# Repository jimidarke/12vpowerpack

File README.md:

# 12 V power pack

A small in-vehicle UPS on one PCB: a 12 V sealed AGM battery floated on the car's charging voltage, a pass-through 12 V output and a 5 V USB-A output that keep running from the battery for a set time after the ignition goes off.

## Status

Design phase. The requirements and architecture were cut back to this vehicle-only design (v3) on 2026-11-13, and the schematic was captured in Flux and checked against the net table that day. On 2026-11-14 the parts were trimmed for a DIY batch of 5 (v3.1), and the schematic was updated and re-checked (77 parts). Later that day capture moved to KiCad 10: the schematic is generated from the net table, and the 100 × 70 mm board is placed, has its first routing pass (power pours and autorouted signals, DRC clean) and carries its silkscreen labels. The routing fixes from the first review, thermal vias and fiducials are in; the checks against parts in hand are still to do (`kicad/README.md`). Nothing has been built or tested. Values marked **[TBC]** in `architecture.md` are still to be confirmed. The earlier two-chemistry design (v2) is in git at tag `v0.2.1`.

## Specification

- **Input:** ignition-switched car 12 V, 13.8–14.4 V nominal with the engine running and 11–14.8 V working. The board starts at about 12.1 V (11.5–12.7 V across part tolerances); once running, the battery carries it through dips and cranking. It is reverse-polarity protected, clamped above 18 V, and the input fuse blows on a sustained 20–22 V. About 5 A continuous and 7 A peak. The battery never feeds back into the car. Not for mains adapters.
- **Battery:** 12 V sealed AGM, 2–12 Ah, charged from the car feed through a current-limiting resistor. There is no charger IC.
- **12 V output:** unregulated: the car feed or the battery less 0.1–0.5 V, so about 10.8–14.8 V (9.9 V worst case at a 5 A peak near the cutoff). 3 A continuous with 5 A peaks, 5.5 mm barrel jack. A car-side fault passes through, up to about 22 V (29 V during a clamped surge).
- **5 V output:** 5.02 V (4.86–5.17 V worst case), 2 A USB-A for loads such as a Pi, router or camera (D+ tied to D−, no charging-port IC).
- **Power control:** outputs stay on for an adjustable time after ignition-off (a firmware setting, default 30 min; 0 = no timeout), then everything switches off until the ignition returns. A hardware low-voltage cutoff near 11.0 V (10.5–11.45 V across part tolerances) protects the battery.

The full voltage and power budget is in [`architecture.md`](architecture.md#voltage-and-power-budget-calc).
- **Monitoring:** socketed Seeed XIAO ESP32-C6 running ESPHome, reporting car voltage, battery voltage, battery temperature, and power in and out from two INA226 current monitors. Red and green status LEDs. No display.
- **Safety:** fuses, the charge limit, reverse-polarity blocking and the low-voltage cutoff are hardware. The board stays safe with the ESP32 removed.
- **Environment:** parts rated −40 to 85 °C.

Full details are in [`requirements.md`](requirements.md).

## Block diagram

```
Car 12 V in ─ fuse ─ TVS ─ ideal diode ─ SYS ─┬─ switch ─ fuse ─ 12 V barrel jack
                                              ├─ 5 V buck ─ USB-A, ESP32
                                              ├─ fuse ─ charge resistor ─┐
                                              └─ ideal diode ────────────┴─ fuse ─ AGM battery
```

## Main parts

| Function | Part |
|---|---|
| Input and battery ideal diodes | TI LM74700-Q1 ×2 with CSD18543Q3A FETs |
| Surge clamp | SMCJ18CA |
| 12 V output switch | Diodes DMP4015SK3 |
| 5 V rail and low-voltage cutoff | TI LMR33630 |
| Current monitors | TI INA226 ×2 |
| Controller | Seeed XIAO ESP32-C6 |
| Battery temperature | DS18B20 probe |

## Repository layout

| Path | Contents |
|---|---|
| [`requirements.md`](requirements.md) | What the board must do |
| [`architecture.md`](architecture.md) | Block diagram, net names, values, power control, voltage and power budget, ESP32 pin map, connectors |
| [`netlist.md`](netlist.md) | Pin-by-pin net table the KiCad schematic is generated from and checked against |
| [`kicad/`](kicad) | KiCad 10 project: generated schematic, board, project library, generator and check scripts ([README](kicad/README.md)) |
| [`plan.md`](plan.md) | Status, part-choice reasoning, cost estimate, how the capture was done, bench test plan |
| [`blocks/`](blocks) | Placement plan (`04-placement*`), layout brief, and the Flux messages and edit lists (history); `retired/` holds the v2 briefs |
| [`datasheets/`](datasheets) | Text extracts of the datasheets the values were taken from |
| [`flux-log.md`](flux-log.md) | Log of the Flux agent runs and credits (Flux archived 2026-11-14) |

The schematic and board are in KiCad 10 (`kicad/`). The earlier Flux capture ([project](https://www.flux.ai/jimidarke/12v-power-manager~zn)) is archived.

## Cost target

≤ C$110 per board at a batch of 5, excluding battery and enclosure. The current price checkpoint is in [`plan.md`](plan.md): the fab fits the SMT parts and the owner hand-solders the through-hole parts and a few easy SMT ones.

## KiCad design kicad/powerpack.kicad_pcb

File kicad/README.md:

# KiCad project

KiCad 10 project for the board: `powerpack.kicad_pro`. Open it in KiCad 10.0.x; the Linux box that generates and checks the files runs 10.0.8, so keep both machines on the same major version.

## Files

| File | Who edits it | What it is |
|---|---|---|
| `powerpack.kicad_sch` | generated: `gen/gen_sch.py` | Schematic, one A2 sheet, one dashed box per module. Every pin carries a net label; there are no wires between parts. **Edit `../netlist.md`, not this file.** |
| `powerpack.kicad_pcb` | the owner, in KiCad | Board. Written once by `gen/gen_pcb.py`, then re-placed on 2026-11-14 by `gen/place_pcb.py` at the owner's request (100 × 70 mm, parts spread out, every label in a clear spot). First routing pass and silkscreen pass (`gen/silk_pcb.py`) on 2026-11-14. Edited by hand from here on, except the silkscreen labels, which come from `silk_pcb.py`; `place_pcb.py` refuses to run once the board has tracks. |
| `powerpack.kicad_pro` | KiCad, plus `gen_pcb.py` once | Project settings, net classes (`Power`: 1.5 mm tracks and 0.8/0.4 mm vias on the power path and GND; `Default`: 0.25 mm; both 0.13 mm clearance, the pours 0.3 mm) and JLCPCB minimums. |
| `sym-lib-table`, `fp-lib-table` | fixed | Add the project library `pwrpack` with `${KIPRJMOD}` paths, so it works on Windows and Linux. |
| `lib/pwrpack.*` | generated: `gen/build_lib.py`, and `gen/build_models.py` for three 3D models | Project symbols (XIAO ESP32-C6, Keystone 3557-2 holder, DMP4015SK3) and footprints (XIAO on two 1×7 sockets, AC10 52 mm, SRP6540, 3557-2, Würth USB-A), with 3D models. |
| `lib/lcsc.*` | `easyeda2kicad` | Raw LCSC downloads that `build_lib.py` converts. The 3D folder is not in git. |
| `out/` | generated, not in git | `expected.json`, KiCad netlist, ERC and DRC reports. |

Every other part uses the stock KiCad 10 libraries.

## Working together over git

- One editor per file. The Linux side regenerates the schematic; the owner owns the board. Don't edit `powerpack.kicad_sch` by hand: the next regeneration overwrites it.
- Close KiCad before `git pull`, reopen after.
- A schematic change: edit `../netlist.md`, run the two scripts below, push. On the laptop: pull, open the board, **Tools → Update PCB from Schematic**. The footprints carry the schematic symbol IDs, so placement and routing are kept.
- `*.kicad_prl` (per-user view state), backups and lock files are in `.gitignore`. `.gitattributes` keeps the KiCad files on LF line endings.

## Commands (Linux box)

```
python3 kicad/gen/gen_sch.py      # netlist.md -> powerpack.kicad_sch
python3 kicad/gen/check_sch.py    # upgrade to the native format, ERC, compare KiCad's netlist with netlist.md
kicad-cli pcb drc --schematic-parity -o kicad/out/drc.rpt kicad/powerpack.kicad_pcb
python3 kicad/gen/build_lib.py    # only when the project library changes
python  kicad/gen/build_models.py # only when a generated 3D model changes; needs CadQuery (pip install cadquery), not KiCad
python3 kicad/gen/gen_pcb.py      # only for a fresh board; refuses to overwrite one
python3 kicad/gen/place_pcb.py    # placement pass on an unrouted board: moves parts and labels from its table, checks, writes
python3 kicad/gen/silk_pcb.py     # silkscreen pass: reference label size and the functional labels from its table; text only, safe on a routed board
```

`place_pcb.py` holds the placement table (courtyard centres in mm from the bottom-left corner, y up). It fails without writing if courtyards overlap, a part leaves the board or enters a mounting-hole keep-out, a label has no clear spot, or a neighbour rule is broken (ideal-diode controller by its FET, INA226 by its shunt, buck parts by U_5V, R_CHG 10 mm from the XIAO, the INA226s and the capacitor banks). Add `--dry-run` to check without writing.

### 3D models

Every part has a model except the test points, the solder jumper and the mounting holes. Three are generated by `gen/build_models.py` from datasheet dimensions, because neither KiCad nor the vendor supplies a usable file (Seeed's XIAO model is behind a GrabCAD login): the XIAO ESP32-C6 on its 8.5 mm sockets (about 15.5 mm tall to the top of the USB-C shell; shield can, USB-C and antenna sizes approximate), the AC10 (drawn 4 mm off the board) and the Schurter UMT 250. They are envelopes for the 3D view and the case, not vendor models: check heights against the parts in hand. F_CHG and U_5V are stock footprints whose model is set on the board (the stock footprints name files KiCad 10 does not ship), so "Update Footprints from Library" would drop those two.

### Silkscreen pass

`gen/silk_pcb.py` sets every reference label to 0.8 mm, moves the three in its `MOVE_REF` table (F_IN, F_BAT, D_TVS) and adds the functional labels in its `LABELS` table (polarity and names at the connectors, fuse ratings, output ratings, test-point net names, notes) as board text in a group named `silk_labels`. The functional labels are 1.0 mm or more, JLCPCB's stated minimum height (0.15 mm line width); the reference labels are below it by the owner's choice, to make room, and may print soft. Each label goes to the free spot nearest its wanted position, clear of pads, courtyards, silkscreen lines and other text; the script fails without writing if there is none. Labels marked `back=True` go on the bottom silkscreen, mirrored. It changes only silkscreen text, so it can run on the routed board, and running it again replaces the group. Add `--dry-run` to check without writing. Labels moved by hand in KiCad are overwritten by the next run, so change the table instead.

### First routing pass

`gen/route.sh` routes a placed, unrouted board (done on 2026-11-14):

1. `gen/route_pcb.py zones` draws the power path as top-layer copper zones (J_CAR_P, VIN_CAR, SYS_IN, SYS, LOAD, VBAT, 12V_SW, 12V_OUT, 5V, SW_5V), a GND zone over the whole bottom layer, J_SLA_P as a bottom zone under J_SLA and F_BAT, and a no-copper rule area under the XIAO antenna.
2. `gen/route_pcb.py dsn` exports a copy for the autorouter with finer net classes and track keep-outs over the necks of the pours, so signal tracks cross them on the bottom layer instead of cutting them. The keep-outs are not in the board.
3. Freerouting 1.9.0 routes the signal nets (0.2 mm tracks; 0.6 mm on 5V, XIAO_5V).
4. `gen/route_pcb.py ses` imports the result, adds the tracks in its `MANUAL` list (CHG_F on the bottom at 1.0 mm, the Q_OR2 gate hop, the INA226 Kelvin sense lines, the links under U_OR1 and U_OR2, the G_OUT bus) and refills the zones.

To redo it after a placement change: restore the unrouted board (`git checkout v0.6.0 -- kicad/powerpack.kicad_pcb` or your own unrouted copy), run `place_pcb.py`, then `bash kicad/gen/route.sh`. Run `silk_pcb.py` last: `place_pcb.py` puts the reference labels back at 1.0 mm and the functional labels are not in the v0.6.0 board. From here on, route by hand in KiCad; these scripts refuse a board that already has tracks.

### JLCPCB files

`python3 gen/fab_jlc.py` (from the repository root: `python3 kicad/gen/fab_jlc.py`) reads the schematic and the board and writes `out/jlcpcb/`: `powerpack-gerbers.zip` (nine layers, drill files in mm with PTH and NPTH separate), `powerpack-bom.csv` (symbols with `Fit` = `fab`, one line per LCSC number) and `powerpack-cpl.csv` (those designators only, mm). It uses the Linux `kicad-cli` when there is one and the Windows binary otherwise, and fails if a fitted part has no LCSC number, is missing from the board or sits on the bottom. Rotations are KiCad's; when JLCPCB's placement preview shows a part turned, add the correction to `ROT_OFFSET` in the script and run it again.

### On the laptop (WSL)

The laptop's WSL has no Linux KiCad. The Windows KiCad 10 binaries run from WSL and do the same job; use them in place of `python3` and `kicad-cli` above for anything that needs `pcbnew` or KiCad itself:

```
K="/mnt/c/Program Files/KiCad/10.0/bin"
"$K/python.exe" kicad/gen/place_pcb.py --dry-run
"$K/python.exe" kicad/gen/silk_pcb.py --dry-run
"$K/kicad-cli.exe" pcb drc --schematic-parity --severity-all -o kicad/out/drc.rpt kicad/powerpack.kicad_pcb
"$K/kicad-cli.exe" pcb render --side top --perspective --rotate "-50,0,0" -o "$(wslpath -w /tmp/3d.png)" kicad/powerpack.kicad_pcb
```

Close the board in KiCad before running anything that writes it. Output paths outside the repository go through `wslpath -w`. `rsvg-convert` is not installed here; `python3 -c "import cairosvg; ..."` converts the exported SVG to PNG.

`gen_sch.py` refuses to write a schematic if a row in `netlist.md` cannot be read, if a pin number and pin name in the table disagree with the KiCad symbol, or if any pin is left without a net or an explicit "open". `check_sch.py` exits non-zero unless every pin matches.

## State on 2026-11-14

- Schematic: 77 parts plus TP1–TP8, H1–H4 and six PWR_FLAGs; 41 nets. ERC clean; netlist matches `netlist.md` pin for pin. Cross-checked net by net against the Flux schematic: identical except that Flux leaves Q_OR2's gate unconnected (see `../flux-log.md`).
- Board: 100 × 70 mm, 2 layers, 4 × M3 at (4, 4), (96, 4), (4, 66), (96, 66), every part placed, first routing pass and the review fixes done (380 track segments, 92 vias, 15 zones, 3 fiducials), silkscreen pass done (reference labels 0.8 mm, 35 labels from `silk_pcb.py`, one of them on the back). DRC: 0 unconnected, 0 shorts, 0 clearance errors, 0 parity errors, 0 courtyard overlaps; 13 "silkscreen clipped by board edge" warnings, all from connector outlines that are meant to reach the edge (J_USBA's shell, and the pin-1 arrows of the three terminal blocks).

## To check on the laptop

1. **Terminal blocks:** J_CAR, J_SLA and J_TEMP are turned 180° so the wire entries face the top edge (seen in a `kicad-cli pcb render`). Pin 1 is now on the right: J_CAR + right, GND left; J_TEMP GND right, DQ middle, 3V3 left. The silkscreen polarity marks under them (`- CAR +`, `- BATT +`, `3V3 DQ GND`) follow these pad nets. Confirm in the 3D viewer, and with a meter on the first board, before trusting the marks.
2. **Footprints drawn from datasheets** (no vendor file): AC10 (52 mm pitch, 1.2 mm holes for 0.8 mm leads), SRP6540 (pads 2.0 × 3.7 mm at ±2.7 mm, read from Bourns' recommended layout), XIAO sockets (rows 15.24 mm apart). Compare with the parts in hand before ordering.
3. **3557-2 holes** are 1.8 mm (from the LCSC footprint); Keystone recommends 1.60 mm. Check against the holder's legs.
4. **J_USBA** overhangs the bottom edge by 4.2 mm, as the generator placed it. Check against the Würth drawing and the case wall whether the shell should stick out that far.
5. **Routing fixes from the review (done 2026-11-14, by script):** `TEMP_DQ` runs on the top layer for its first 13 mm from J_TEMP pin 2 (it used to seal the bottom GND plane's strip above J_TEMP, the only wide way to J_CAR pin 2); D_TVS pin 2 has a copper patch and 5 vias; C_IN5 and C_HF5 have 3 GND vias each, C_O1–C_O4 two each. A sheet-resistance solve of the bottom plane at 7 A from J_CAR pin 2 gives 2.8 mΩ and a peak of 2.9 A/mm away from the pins (was 4.6 mΩ and 4.8 A/mm). Look these over in KiCad; move the `TEMP_DQ` via further along its track if a later layout frees the top layer there.
6. **Thermal vias and fiducials (done 2026-11-14, by script):** Q_OR1 and Q_OR2 have six vias each and Q_OUT eight, onto same-net copper islands on the bottom layer (U_5V has the footprint's eight into the GND plane). Three of each set sit in the pad; if they wick solder at assembly, the vias beside the pad still carry the heat. FID1–FID3 are board-only footprints, so they do not appear in the schematic or the BOM. Still optional: a top-layer GND fill with stitching vias, and tidying the autorouted signal tracks. The power pours follow `blocks/03-layout-brief.md` except where a part's own pads are narrower (the LOAD feed to the buck is 1.6 mm; the VBAT charge leg over F_BAT is 2.1 mm).

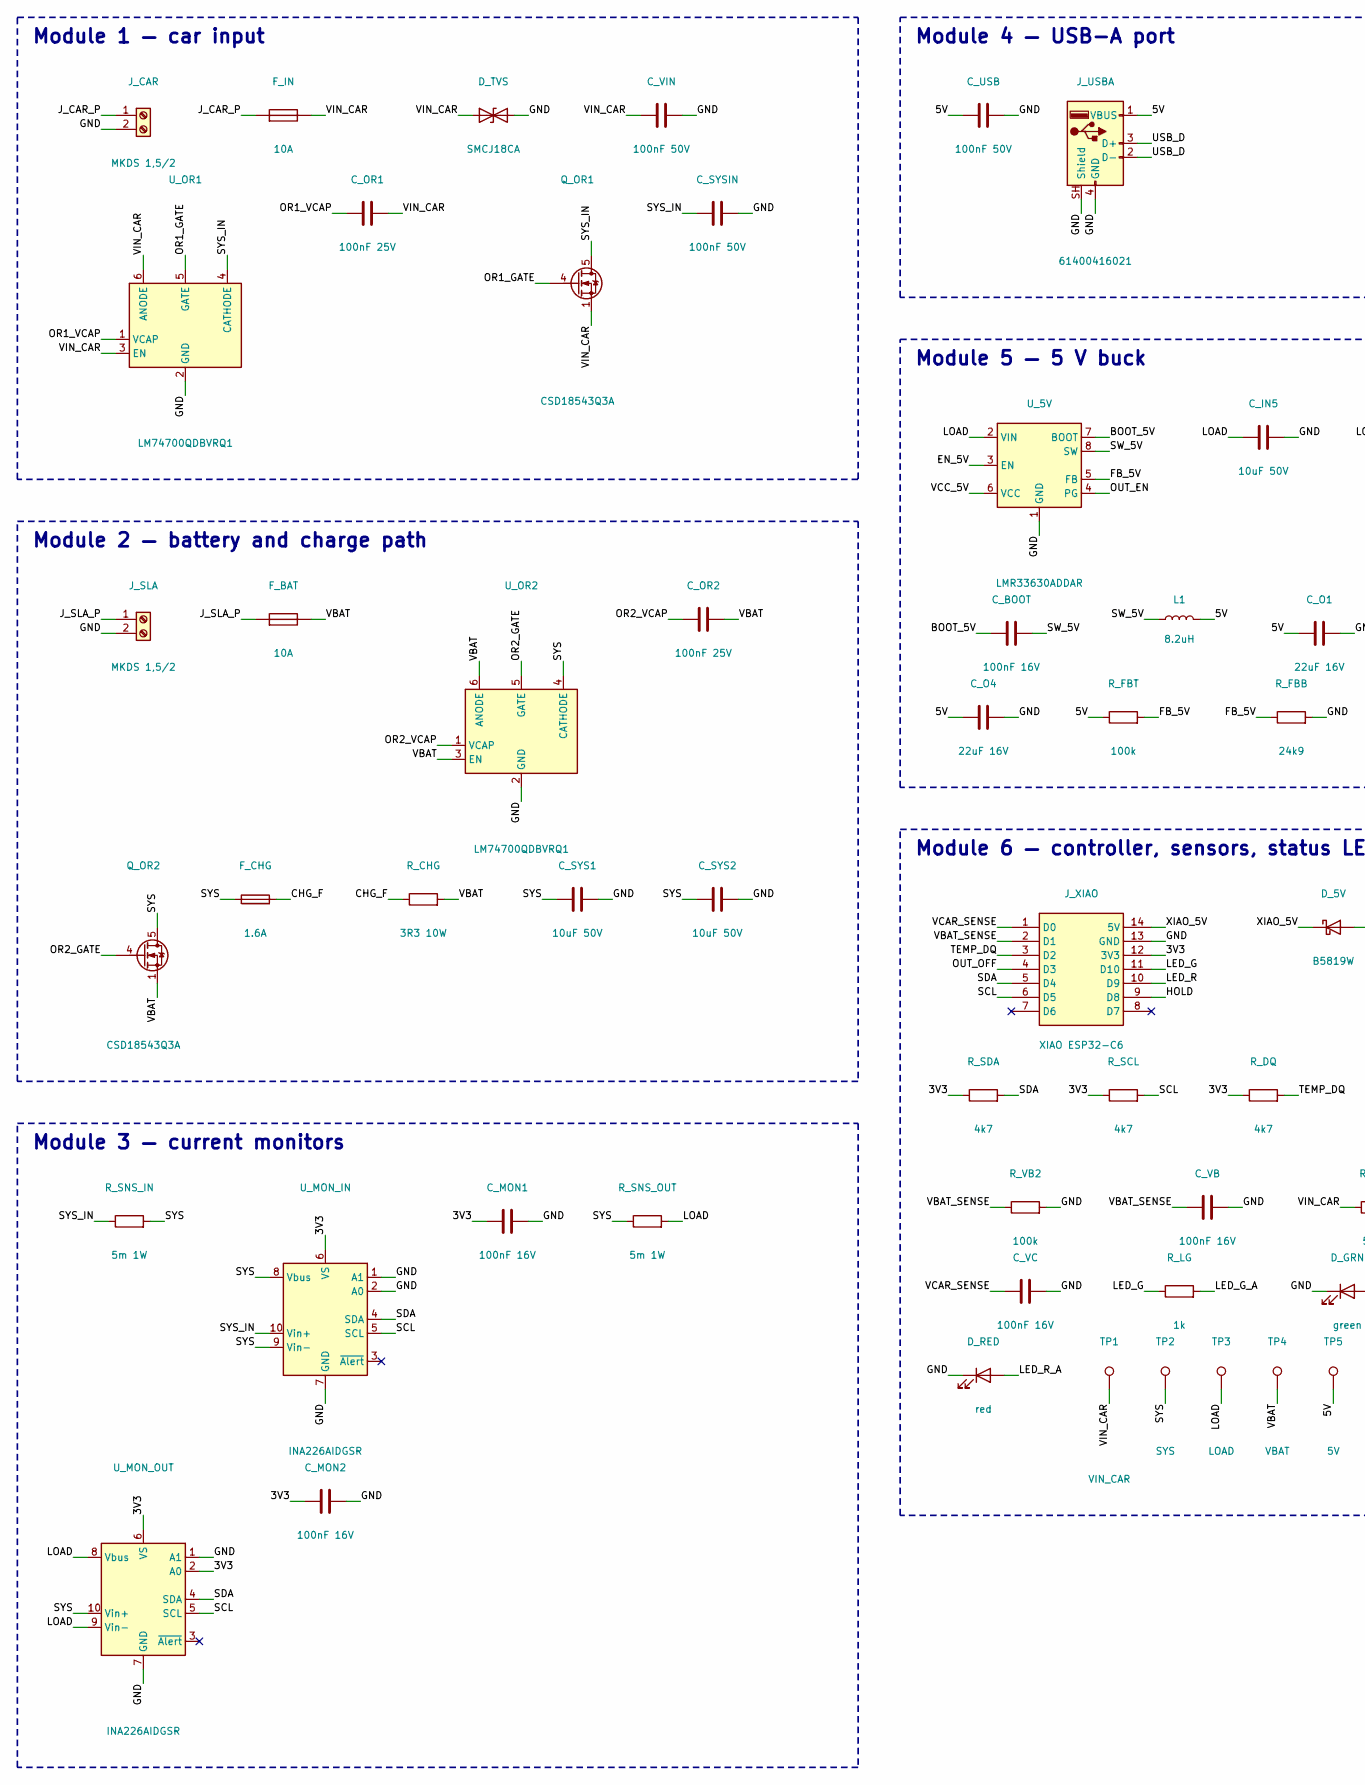
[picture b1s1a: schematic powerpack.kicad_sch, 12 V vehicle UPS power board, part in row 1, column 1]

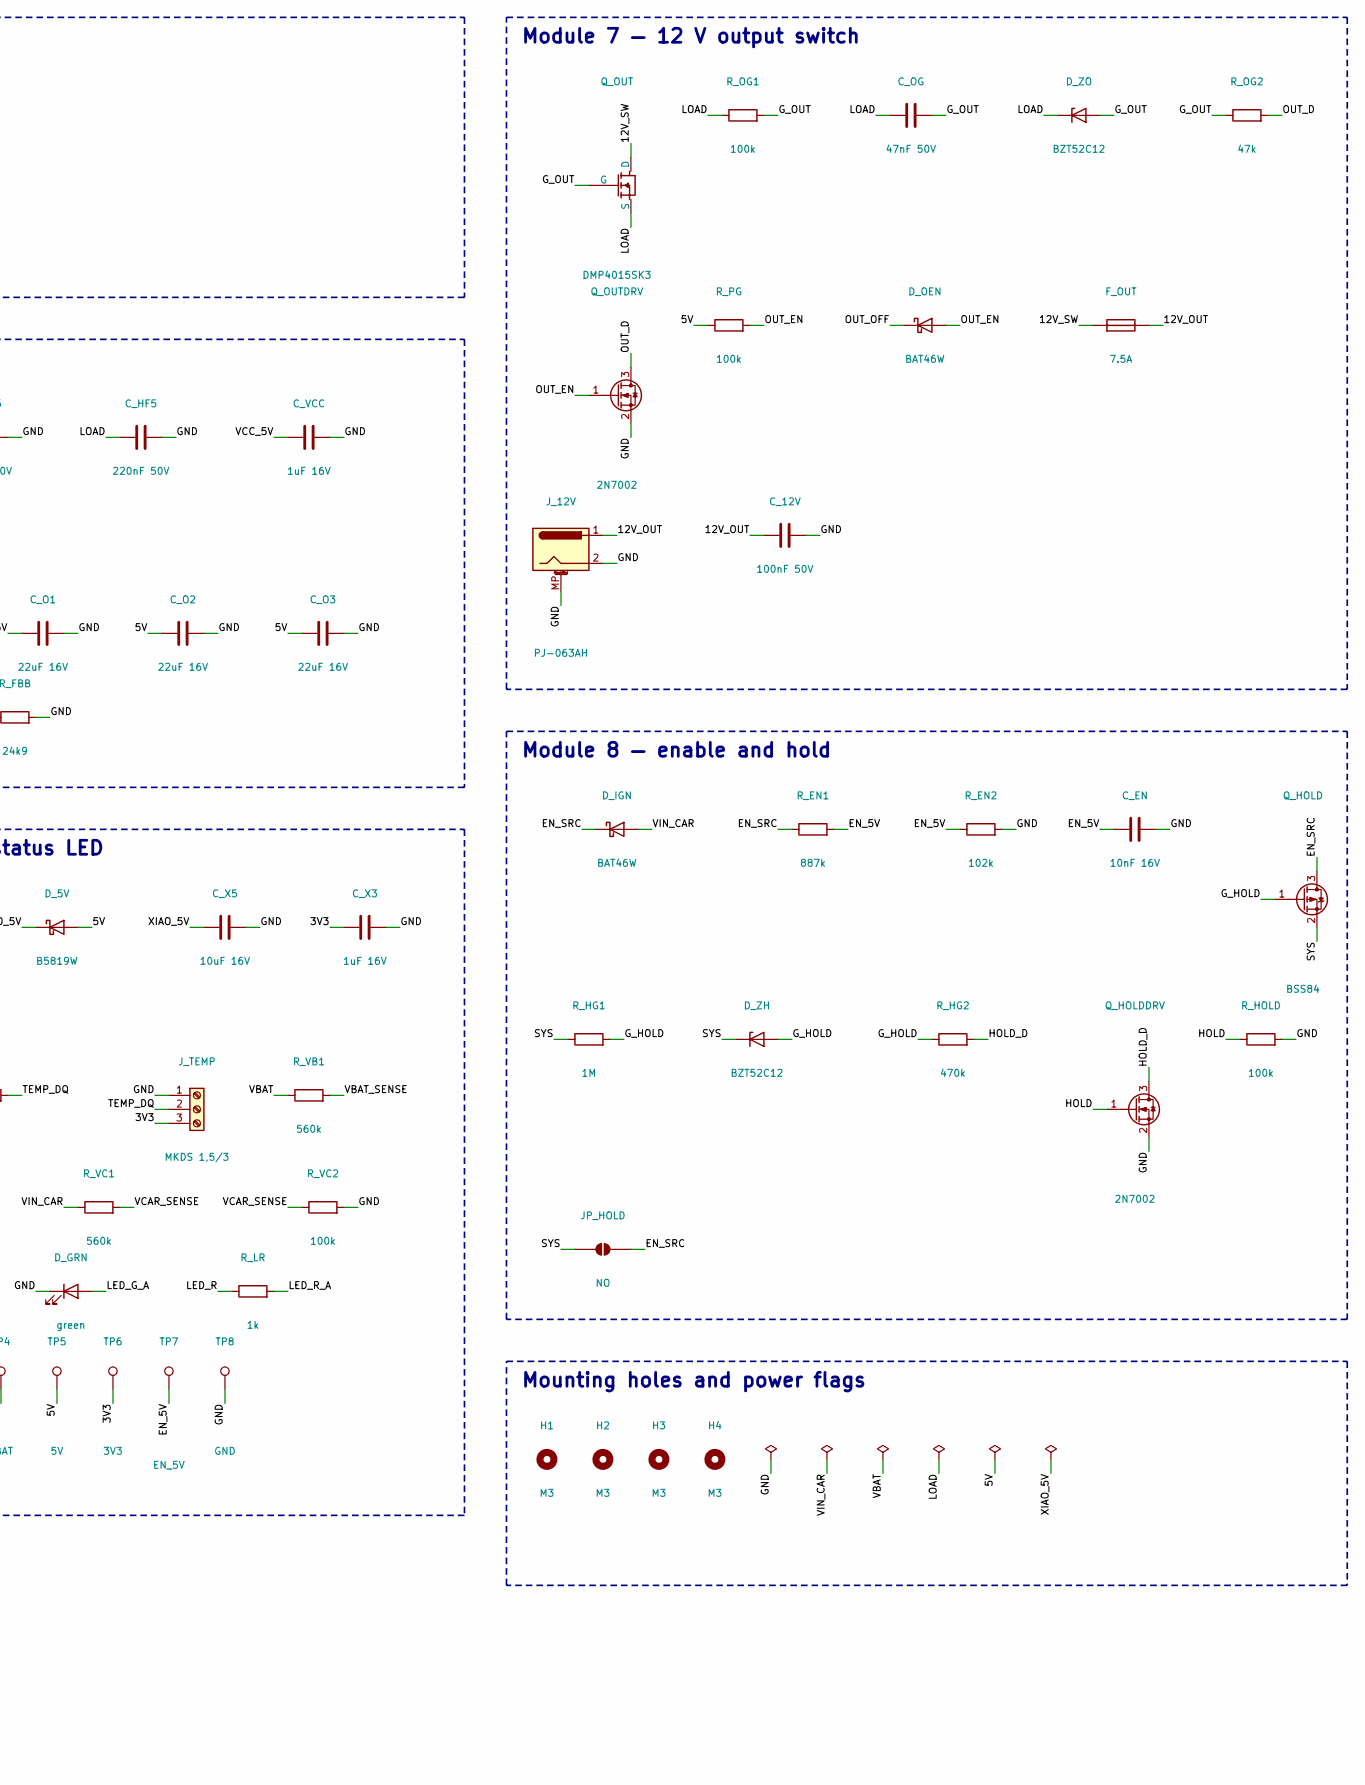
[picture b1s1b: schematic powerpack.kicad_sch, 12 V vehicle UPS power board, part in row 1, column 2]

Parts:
C_12V: 100nF 50V; C_0603_1608Metric; MPN Yageo CC0603KRX7R9BB104, 100 nF 50 V X7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; LCSC C14663
C_BOOT: 100nF 16V; C_0603_1608Metric; MPN Yageo CC0603KRX7R9BB104, 100 nF 50 V X7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; LCSC C14663
C_EN: 10nF 16V; C_0603_1608Metric; MPN FH 0603B103K500NT, 10 nF 50 V X7R 0603; LCSC C57112
C_HF5: 220nF 50V; C_0805_2012Metric; MPN Samsung CL21B224KBFNNNE, 220 nF 50 V X7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; LCSC C5378
C_IN5: 10uF 50V; C_1206_3216Metric; MPN Samsung CL31A106KBHNNNE, 10 µF 50 V X5R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; LCSC C13585
C_MON1, C_MON2: 100nF 16V; C_0603_1608Metric; MPN Yageo CC0603KRX7R9BB104, 100 nF 50 V X7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; LCSC C14663
C_O1, C_O2, C_O3, C_O4: 22uF 16V; C_1206_3216Metric; MPN Samsung CL31A226KAHNNNE, 22 µF 25 V X5R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; LCSC C12891
C_OG: 47nF 50V; C_0603_1608Metric; MPN Samsung CL10B473KB8NNNC, 47 nF 50 V X7R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; LCSC C1622
C_OR1, C_OR2: 100nF 25V; C_0603_1608Metric; MPN Yageo CC0603KRX7R9BB104, 100 nF 50 V X7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; LCSC C14663
C_SYS1, C_SYS2: 10uF 50V; C_1206_3216Metric; MPN Samsung CL31A106KBHNNNE, 10 µF 50 V X5R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; LCSC C13585
C_SYSIN: 100nF 50V; C_0603_1608Metric; MPN Yageo CC0603KRX7R9BB104, 100 nF 50 V X7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; LCSC C14663
C_USB: 100nF 50V; C_0603_1608Metric; MPN Yageo CC0603KRX7R9BB104, 100 nF 50 V X7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; LCSC C14663
C_VB: 100nF 16V; C_0603_1608Metric; MPN Yageo CC0603KRX7R9BB104, 100 nF 50 V X7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; LCSC C14663
C_VC: 100nF 16V; C_0603_1608Metric; MPN Yageo CC0603KRX7R9BB104, 100 nF 50 V X7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; LCSC C14663
C_VCC: 1uF 16V; C_0603_1608Metric; MPN Samsung CL10A105KB8NNNC, 1 µF 50 V X5R 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; LCSC C15849
C_VIN: 100nF 50V; C_0603_1608Metric; MPN Yageo CC0603KRX7R9BB104, 100 nF 50 V X7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; LCSC C14663
C_X3: 1uF 16V; C_0603_1608Metric; MPN Samsung CL10A105KB8NNNC, 1 µF 50 V X5R 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; LCSC C15849
C_X5: 10uF 16V; C_0805_2012Metric; MPN Samsung CL21A106KAYNNNE, 10 µF 25 V X5R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; LCSC C15850
D_5V: B5819W; D_SOD-123; MPN MDD B5819W; LCSC C64885
D_GRN: green; LED_0603_1608Metric; MPN KENTO KT-0603YG; LCSC C2289
D_IGN: BAT46W; D_SOD-123; MPN Diodes BAT46W-7-F; LCSC C83152
D_OEN: BAT46W; D_SOD-123; MPN Diodes BAT46W-7-F; LCSC C83152
D_RED: red; LED_0603_1608Metric; MPN KENTO KT-0603R; LCSC C2286
D_TVS: SMCJ18CA; D_SMC; MPN Diodes SMCJ18CA-13-F; LCSC C135149
D_ZH: BZT52C12; D_SOD-123; MPN CJ BZT52C12; LCSC C43491
D_ZO: BZT52C12; D_SOD-123; MPN CJ BZT52C12; LCSC C43491
F_BAT: 10A; Fuseholder_Blade_ATO_Keystone_3557-2; MPN Keystone 3557-2
F_CHG: 1.6A; Fuse_Schurter_UMT250; MPN Schurter UMT 250, 1.6 A time-lag (3403.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
F_IN: 10A; Fuseholder_Blade_ATO_Keystone_3557-2; MPN Keystone 3557-2
F_OUT: 7.5A; Fuseholder_Blade_ATO_Keystone_3557-2; MPN Keystone 3557-2
H1, H2, H3, H4: M3; MountingHole_3.2mm_M3
JP_HOLD: NO; SolderJumper-2_P1.3mm_Open_RoundedPad1.0x1.5mm
J_12V: PJ-063AH; BarrelJack_CUI_PJ-063AH_Horizontal; MPN Same Sky PJ-063AH
J_CAR: MKDS 1,5/2; TerminalBlock_Phoenix_MKDS-1,5-2_1x02_P5.00mm_Horizontal; MPN Phoenix Contact MKDS 1,5/2 (1715022), 2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; LCSC C3817933
J_SLA: MKDS 1,5/2; TerminalBlock_Phoenix_MKDS-1,5-2_1x02_P5.00mm_Horizontal; MPN Phoenix Contact MKDS 1,5/2 (1715022), 2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; LCSC C3817933
J_TEMP: MKDS 1,5/3; TerminalBlock_Phoenix_MKDS-1,5-3_1x03_P5.00mm_Horizontal; MPN Phoenix Contact MKDS 1,5/3 (1715035), 3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; LCSC C6787349
J_USBA: 61400416021; USB_A_Wuerth_61400416021_Horizontal; MPN Würth 61400416021
J_XIAO: XIAO ESP32-C6; XIAO_ESP32C6_Socketed_2x1x07_P2.54mm; MPN Seeed XIAO ESP32-C6
L1: 8.2uH; L_Bourns_SRP6540_7.2x6.5mm; MPN Bourns SRP6540-8R2M; LCSC C2041807
Q_HOLD: BSS84; SOT-23; MPN LRC LBSS84LT1G; LCSC C8492
Q_HOLDDRV: 2N7002; SOT-23; MPN CJ 2N7002; LCSC C8545
Q_OR1, Q_OR2: CSD18543Q3A; VSON-8_3.3x3.3mm_P0.65mm_NexFET; MPN TI CSD18543Q3A; LCSC C840100
Q_OUT: DMP4015SK3; TO-252-2; MPN Diodes DMP4015SK3-13; LCSC C513222
Q_OUTDRV: 2N7002; SOT-23; MPN CJ 2N7002; LCSC C8545
R_CHG: 3R3 10W; R_Axial_Vishay_AC10_EK_L44.0mm_D8.0mm_P52.00mm; MPN Vishay AC10000003308JAB00
R_DQ: 4k7; R_0603_1608Metric; MPN UNI-ROYAL 4.7 kΩ; LCSC C23162
R_EN1: 887k; R_0603_1608Metric; MPN RALEC RTT038873FTP, 887 kΩ; LCSC C103858
R_EN2: 102k; R_0603_1608Metric; MPN UNI-ROYAL 102 kΩ; LCSC C22858
R_FBB: 24k9; R_0603_1608Metric; MPN UNI-ROYAL 24.9 kΩ; LCSC C25962
R_FBT: 100k; R_0603_1608Metric; MPN UNI-ROYAL 0603WAF1003T5E, 100 kΩ; LCSC C25803
R_HG1: 1M; R_0603_1608Metric; MPN UNI-ROYAL 1 MΩ; LCSC C22935
R_HG2: 470k; R_0603_1608Metric; MPN UNI-ROYAL 470 kΩ; LCSC C23178
R_HOLD: 100k; R_0603_1608Metric; MPN UNI-ROYAL 0603WAF1003T5E, 100 kΩ; LCSC C25803
R_LG: 1k; R_0603_1608Metric; MPN UNI-ROYAL 1 kΩ; LCSC C21190
R_LR: 1k; R_0603_1608Metric; MPN UNI-ROYAL 1 kΩ; LCSC C21190
R_OG1: 100k; R_0603_1608Metric; MPN UNI-ROYAL 0603WAF1003T5E, 100 kΩ; LCSC C25803
R_OG2: 47k; R_0603_1608Metric; MPN UNI-ROYAL 47 kΩ; LCSC C25819
R_PG: 100k; R_0603_1608Metric; MPN UNI-ROYAL 0603WAF1003T5E, 100 kΩ; LCSC C25803
R_SCL: 4k7; R_0603_1608Metric; MPN UNI-ROYAL 4.7 kΩ; LCSC C23162
R_SDA: 4k7; R_0603_1608Metric; MPN UNI-ROYAL 4.7 kΩ; LCSC C23162
R_SNS_IN: 5m 1W; R_2512_6332Metric; MPN RALEC LR2512-22R005F4, 5 mΩ 1 % 2 W; LCSC C108931
R_SNS_OUT: 5m 1W; R_2512_6332Metric; MPN RALEC LR2512-22R005F4, 5 mΩ 1 % 2 W; LCSC C108931
R_VB1: 560k; R_0603_1608Metric; MPN UNI-ROYAL 560 kΩ; LCSC C23203
R_VB2: 100k; R_0603_1608Metric; MPN UNI-ROYAL 0603WAF1003T5E, 100 kΩ; LCSC C25803
R_VC1: 560k; R_0603_1608Metric; MPN UNI-ROYAL 560 kΩ; LCSC C23203
R_VC2: 100k; R_0603_1608Metric; MPN UNI-ROYAL 0603WAF1003T5E, 100 kΩ; LCSC C25803
TP1: VIN_CAR; TestPoint_Pad_D1.5mm
TP2: SYS; TestPoint_Pad_D1.5mm
TP3: LOAD; TestPoint_Pad_D1.5mm
TP4: VBAT; TestPoint_Pad_D1.5mm
TP5: 5V; TestPoint_Pad_D1.5mm
TP6: 3V3; TestPoint_Pad_D1.5mm
TP7: EN_5V; TestPoint_Pad_D1.5mm
TP8: GND; TestPoint_Pad_D1.5mm
U_5V: LMR33630ADDAR; Texas_HSOP-8-1EP_3.9x4.9mm_P1.27mm_ThermalVias; MPN TI LMR33630ADDAR; LCSC C841384
U_MON_IN: INA226AIDGSR; TSSOP-10_3x3mm_P0.5mm; MPN TI INA226AIDGSR; LCSC C49851
U_MON_OUT: INA226AIDGSR; TSSOP-10_3x3mm_P0.5mm; MPN TI INA226AIDGSR; LCSC C49851
U_OR1, U_OR2: LM74700QDBVRQ1; SOT-23-6; MPN TI LM74700QDBVRQ1; LCSC C2941042

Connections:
/3V3: C_MON1.1, C_MON2.1, C_X3.1, J_TEMP.3, J_XIAO.12 (3V3), R_DQ.1, R_SCL.1, R_SDA.1, TP6.1, U_MON_IN.6 (VS), U_MON_OUT.2 (A0), U_MON_OUT.6 (VS)
/5V: C_O1.1, C_O2.1, C_O3.1, C_O4.1, C_USB.1, D_5V.2 (A), J_USBA.1 (VBUS), L1.2, R_FBT.1, R_PG.1, TP5.1
/12V_OUT: C_12V.1, F_OUT.3, F_OUT.4, J_12V.1
/12V_SW: F_OUT.1, F_OUT.2, Q_OUT.2 (D)
/BOOT_5V: C_BOOT.1, U_5V.7 (BOOT)
/CHG_F: F_CHG.2, R_CHG.1
/EN_5V: C_EN.1, R_EN1.2, R_EN2.1, TP7.1, U_5V.3 (EN)
/EN_SRC: D_IGN.1 (K), JP_HOLD.2 (B), Q_HOLD.3 (D), R_EN1.1
/FB_5V: R_FBB.1, R_FBT.2, U_5V.5 (FB)
/GND: C_12V.2, C_EN.2, C_HF5.2, C_IN5.2, C_MON1.2, C_MON2.2, C_O1.2, C_O2.2, C_O3.2, C_O4.2, C_SYS1.2, C_SYS2.2, C_SYSIN.2, C_USB.2, C_VB.2, C_VC.2, C_VCC.2, C_VIN.2, C_X3.2, C_X5.2, D_GRN.1 (K), D_RED.1 (K), D_TVS.2 (A2), J_12V.2, J_12V.MP (MountPin), J_CAR.2, J_SLA.2, J_TEMP.1, J_USBA.4 (GND), J_USBA.SH (Shield), J_XIAO.13 (GND), Q_HOLDDRV.2 (S), Q_OUTDRV.2 (S), R_EN2.2, R_FBB.2, R_HOLD.2, R_VB2.2, R_VC2.2, TP8.1, U_5V.1 (GND), U_5V.9 (GND), U_MON_IN.1 (A1), U_MON_IN.2 (A0), U_MON_IN.7 (GND), U_MON_OUT.1 (A1), U_MON_OUT.7 (GND), U_OR1.2 (GND), U_OR2.2 (GND)
/G_HOLD: D_ZH.2 (A), Q_HOLD.1 (G), R_HG1.2, R_HG2.1
/G_OUT: C_OG.2, D_ZO.2 (A), Q_OUT.1 (G), R_OG1.2, R_OG2.1
/HOLD: J_XIAO.9 (D8), Q_HOLDDRV.1 (G), R_HOLD.1
/HOLD_D: Q_HOLDDRV.3 (D), R_HG2.2
/J_CAR_P: F_IN.1, F_IN.2, J_CAR.1
/J_SLA_P: F_BAT.1, F_BAT.2, J_SLA.1
/LED_G: J_XIAO.11 (D10), R_LG.1
/LED_G_A: D_GRN.2 (A), R_LG.2
/LED_R: J_XIAO.10 (D9), R_LR.1
/LED_R_A: D_RED.2 (A), R_LR.2
/LOAD: C_HF5.1, C_IN5.1, C_OG.1, D_ZO.1 (K), Q_OUT.3 (S), R_OG1.1, R_SNS_OUT.2, TP3.1, U_5V.2 (VIN), U_MON_OUT.8 (Vbus), U_MON_OUT.9 (Vin-)
/OR1_GATE: Q_OR1.4 (G), U_OR1.5 (GATE)
/OR1_VCAP: C_OR1.1, U_OR1.1 (VCAP)
/OR2_GATE: Q_OR2.4 (G), U_OR2.5 (GATE)
/OR2_VCAP: C_OR2.1, U_OR2.1 (VCAP)
/OUT_D: Q_OUTDRV.3 (D), R_OG2.2
/OUT_EN: D_OEN.2 (A), Q_OUTDRV.1 (G), R_PG.2, U_5V.4 (PG)
/OUT_OFF: D_OEN.1 (K), J_XIAO.4 (D3)
/SCL: J_XIAO.6 (D5), R_SCL.2, U_MON_IN.5 (SCL), U_MON_OUT.5 (SCL)
/SDA: J_XIAO.5 (D4), R_SDA.2, U_MON_IN.4 (SDA), U_MON_OUT.4 (SDA)
/SW_5V: C_BOOT.2, L1.1, U_5V.8 (SW)
/SYS: C_SYS1.1, C_SYS2.1, D_ZH.1 (K), F_CHG.1, JP_HOLD.1 (A), Q_HOLD.2 (S), Q_OR2.5 (D), R_HG1.1, R_SNS_IN.2, R_SNS_OUT.1, TP2.1, U_MON_IN.8 (Vbus), U_MON_IN.9 (Vin-), U_MON_OUT.10 (Vin+), U_OR2.4 (CATHODE)
/SYS_IN: C_SYSIN.1, Q_OR1.5 (D), R_SNS_IN.1, U_MON_IN.10 (Vin+), U_OR1.4 (CATHODE)
/TEMP_DQ: J_TEMP.2, J_XIAO.3 (D2), R_DQ.2
/USB_D: J_USBA.2 (D-), J_USBA.3 (D+)
/VBAT: C_OR2.2, F_BAT.3, F_BAT.4, Q_OR2.1 (S), Q_OR2.2 (S), Q_OR2.3 (S), R_CHG.2, R_VB1.1, TP4.1, U_OR2.3 (EN), U_OR2.6 (ANODE)
/VBAT_SENSE: C_VB.1, J_XIAO.2 (D1), R_VB1.2, R_VB2.1
/VCAR_SENSE: C_VC.1, J_XIAO.1 (D0), R_VC1.2, R_VC2.1
/VCC_5V: C_VCC.1, U_5V.6 (VCC)
/VIN_CAR: C_OR1.2, C_VIN.1, D_IGN.2 (A), D_TVS.1 (A1), F_IN.3, F_IN.4, Q_OR1.1 (S), Q_OR1.2 (S), Q_OR1.3 (S), R_VC1.1, TP1.1, U_OR1.3 (EN), U_OR1.6 (ANODE)
/XIAO_5V: C_X5.1, D_5V.1 (K), J_XIAO.14 (5V)

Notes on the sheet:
Module 7 — 12 V output switch
Module 5 — 5 V buck
Module 4 — USB-A port
Mounting holes and power flags
Module 6 — controller, sensors, status LED
Module 1 — car input
Module 3 — current monitors
Module 2 — battery and charge path
Module 8 — enable and hold

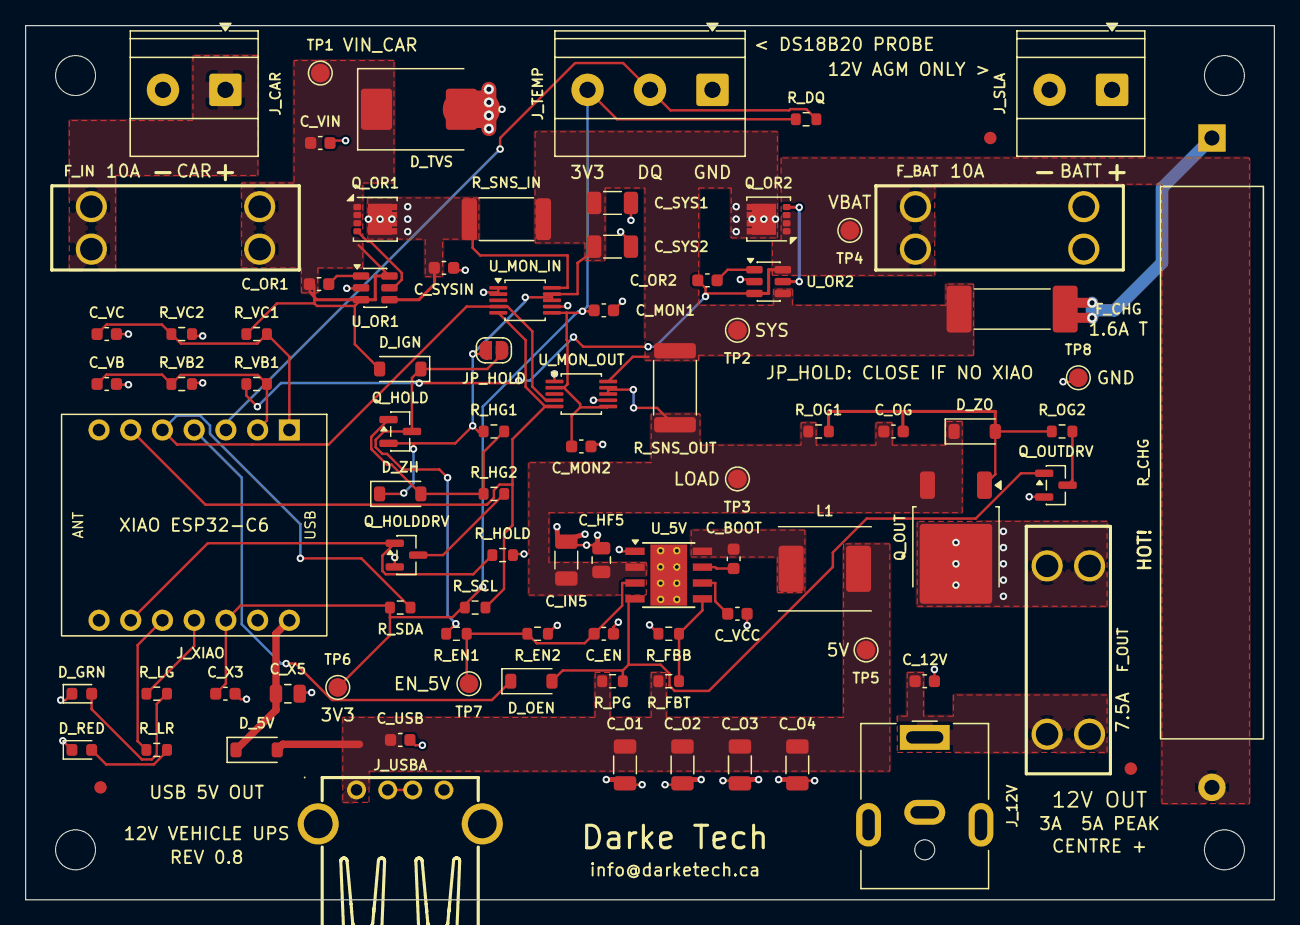
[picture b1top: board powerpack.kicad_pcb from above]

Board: 2 copper layers, 100.0 x 70.0 mm, 92 parts (0 on the bottom side), 41 nets.

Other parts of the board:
FID1, FID2, FID3: Fiducial; Fiducial_1mm_Mask2mm

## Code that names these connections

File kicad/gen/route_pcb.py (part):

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    ("OR2_GATE", "F", 0.25, [(60.95, 55.45), (61.95, 55.45)]),
    ("OR2_GATE", "B", 0.25, [(61.95, 55.45), (61.95, 49.5)]),
    ("OR2_GATE", "F", 0.25, [(61.95, 49.5), (60.65, 49.5)]),
    # The two VBAT pins of U_OR2 and the two VIN_CAR pins of U_OR1, joined under the package.
    ("VBAT", "F", 0.25, [(58.35, 48.55), (59.5, 48.55), (59.5, 50.45), (60.65, 50.45)]),
    ("VIN_CAR", "F", 0.25, [(26.85, 48.05), (28.0, 48.05), (28.0, 49.95), (29.15, 49.95)]),
    # U_OR1 pin 3 to the VIN_CAR pour at C_OR1; U_OR1 pin 4 to the SYS_IN pour at C_SYSIN.
    ("VIN_CAR", "F", 0.25, [(26.85, 48.05), (23.3, 48.05), (22.75, 48.7)]),
    ("SYS_IN", "F", 0.25, [(29.15, 48.05), (31.5, 48.05), (32.75, 49.3), (32.75, 50.3)]),
    # Kelvin sense lines of U_MON_IN: pin 10 to the SYS_IN pad of R_SNS_IN, pins 8/9 to SYS at C_SYS2.
    ("SYS_IN", "F", 0.2, [(42.15, 49.0), (43.4, 49.0), (43.4, 51.6), (36.4, 51.6), (35.8, 52.2), (35.8, 53.0)]),
    ("SYS", "F", 0.2, [(42.15, 48.5), (44.2, 48.5), (44.2, 51.0), (45.3, 51.8)]),
    # G_OUT across the top of the gate parts: R_OG1, C_OG, D_ZO.
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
